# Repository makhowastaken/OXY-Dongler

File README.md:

# OXY-Dongler
Dongle to allow Game Boy Advance peripherals to be used on a Game Boy Micro

You can order the PCB files from Oshpark by using my shared projects link for the [solid board](https://oshpark.com/projects/G7eothoV) or the [breakaway board](https://oshpark.com/shared_projects/KbXcIG3Z) or you can upload the gerber zip archives in the [gerbers directory](https://github.com/makhowastaken/OXY-Dongler/tree/master/gerbers) to any of your choice of PCB fabricator. Oshpark will probably be the cheapest for small QTYs (3 for $1.40). 

There are two versions, one is a solid board similar to [BlindEye's version](https://www.tindie.com/products/hidarite/link-cable-adapter-for-game-boy-micro/) but with a few small changes implemented that should make the board easier to assemble and stronger. I also added a pinout for the charge pins on the Micro EXP connector but they are not connected to the AGB EXP connector. My boards are slightly bigger than BlindEye's and do not have the mounting holes for the 3D printed case and such will not be compatible. I will likely revise these boards after testing them. 

The other version of the board is identical except that it has several holes drilled down the middle to allow the PCB to be separated into two halves. You'd then need to connect the two halves with six separate conductors. I haven't found a good off-the-shelf part for this but a small section of ribbon cable should work fine. 

Both ports need to be soldered on the same side of the board. I added another set of contacts to the breakaway version so that the port may be soldered in the middle of the board instead of on top, but the orientation of the port itself has not changed. 

To assemble this, you'll need two parts plus these PCBs.
1. A cheap USB charging cable for the Micro: https://www.aliexpress.com/item/33024882598.html
2. A bare AGB/AGS EXT port: https://www.aliexpress.com/item/32815359689.html

And to assemble, see this video I made: https://youtu.be/QlkQgUIXweQ

The video is of BlindEye's PCBs but the assembly and function will be identical.

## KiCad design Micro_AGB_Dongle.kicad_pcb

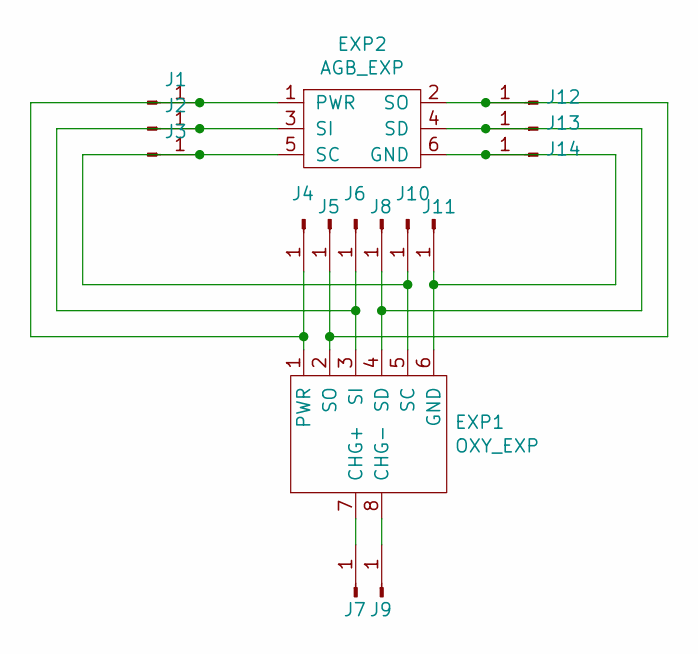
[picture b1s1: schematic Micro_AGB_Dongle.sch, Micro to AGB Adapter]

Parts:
EXP1: OXY_EXP
EXP2: AGB_EXP
J1, J2, J3, J4, J5, J6, J7, J8, J9, J10, J11, J12, J13, J14: Conn_01x01_Male; PinHeader_1x01_P1.00mm_Vertical

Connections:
unnamed: EXP1.1 (PWR), EXP2.1 (PWR), J1.1, J4.1
unnamed: EXP1.2 (SO), EXP2.2 (SO), J5.1, J12.1
unnamed: EXP1.3 (SI), EXP2.3 (SI), J2.1, J6.1
unnamed: EXP1.4 (SD), EXP2.4 (SD), J8.1, J13.1
unnamed: EXP1.5 (SC), EXP2.5 (SC), J3.1, J10.1
unnamed: EXP1.6 (GND), EXP2.6 (GND), J11.1, J14.1
unnamed: EXP1.7 (CHG+), J7.1
unnamed: EXP1.8 (CHG-), J9.1

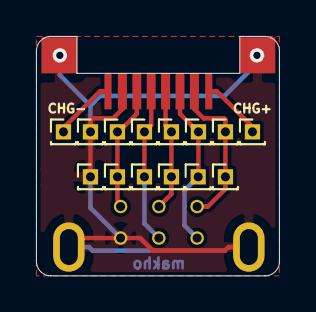
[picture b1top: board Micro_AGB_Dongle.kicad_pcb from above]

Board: 2 copper layers, 13.5 x 13.3 mm, 16 parts (0 on the bottom side), 8 nets.

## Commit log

2019-12-21 Add files via upload
    v1.0 created
2019-12-21 Add files via upload
    added PCB renders of v1.0
2019-12-21 Update README.md
    initial readme
2019-12-21 Update README.md
    added shared projects link for oshpark
